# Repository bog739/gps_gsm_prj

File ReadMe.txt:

-> machine module is for generic board in contrast with pyb lib

-> This project was started with gps and gsm modules
on a simple plastic board with attached cables for
TTL conversion for USB and Pycharm was used to link up
with devices.

-> In meantime the development of this project started on Pi pico, and
Thonny IDE is used afterwards, MicroPython plugin for Pycharm is not
so great. Although, Thonny IDE needs some improvement for USB communication, but for this
issue a  reset button was attached for Pi pico to re-enable the communication.

-> There is a problem for matching modules to have a perfect synchronization as close as possible,
when working on a real PCB board, taking into consideration that components are not place as close as
possible to each other's pins which traces' inductance can increase substantialy.

-> For gps module a simple solution is to use a loop to wait for gps' data to come, but
this method is not very precise because of uncertainty of synchronization between python program and
how quick gps sends its data in its specific format.

-> Basic functions read, readline, write from UART module of micropython do not work
as expected, by using uasyncio lib with StreamWriter and StreamReader classes only then characters
are stored in UART buffer and read or written as wanted. From StreamWriter class use drain function after a write func
to output buffer data or just awrite method(it uses internally drain()).

Possibilities for gsm Ctrl-Z problem:
-> It takes some time to process, send and return a status for SMS so an
immediate read doesn't report anything. A subsequent read may.
I would keep issuing read until you get something other than nothing.

-> The GA6 isn't actioning the Ctrl-Z. Issuing a write 'ABC\r' and a read
should show if it's still in its waiting for message mode.

-> For some reason the Ctrl-Z isn't being sent to the GA6.
Again, issuing a write 'ABC\r' and a read should show if it's still in its waiting for message mode.

-> Looking at what gets sent out with a Terminal Emulator
instead of the GA6 should confirm whether Ctrl-Z's are sent or not.
Being the ASCII code for "EOF - End of File' imeans it could be handled differently
to printable ASCII codes, but if that's the case would how any other GA6 user has achieved it.

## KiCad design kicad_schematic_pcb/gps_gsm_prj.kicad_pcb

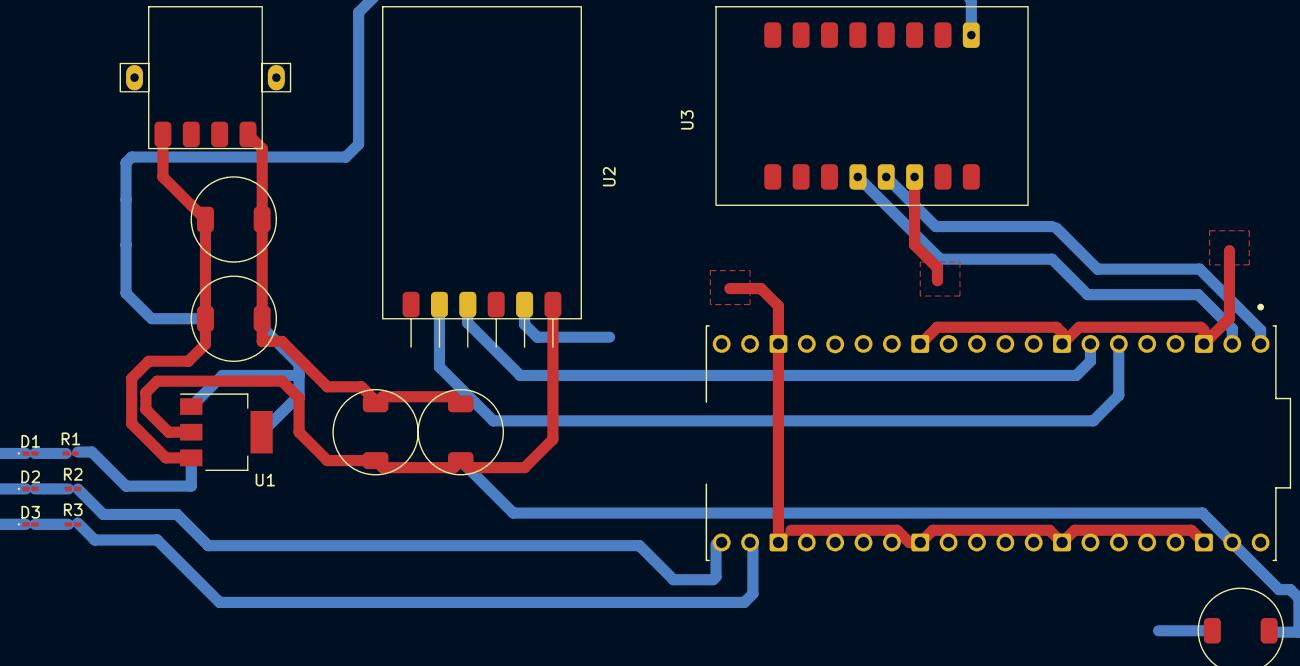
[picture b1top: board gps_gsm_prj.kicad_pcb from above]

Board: 2 copper layers, 16 parts (0 on the bottom side), 8 nets.

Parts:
A1: SC0915; MODULE_SC0915
C1, C2, C3, C4, C5: 10uF; cap
D1: LED_power; LED_0201_0603Metric_Pad0.64x0.40mm_HandSolder
D2: LED_gps; LED_0201_0603Metric_Pad0.64x0.40mm_HandSolder
D3: LED_gsm; LED_0201_0603Metric_Pad0.64x0.40mm_HandSolder
J1: USB_B; USB
R1: 300Ω; R_0201_0603Metric_Pad0.64x0.40mm_HandSolder
R2, R3: 10kΩ; R_0201_0603Metric_Pad0.64x0.40mm_HandSolder
U1: LD1117S33TR_SOT223; SOT-223-3_TabPin2
U2: Pmod_GPS; gps
U3: GSM_module; gsm

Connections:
/VU1_3V3: A1.39 (VSYS), C3.1, C4.1, C5.1, U1.2 (VO), U2.6 (Vcc)
/Vin_5V: C1.1, C2.1, J1.1 (VBUS), U1.3 (VI), U3.8 (Vcc)
GND: C1.2, C2.2, C3.2, C4.2, J1.4 (GND), U1.1 (GND), U1.2 (VO)
GND1: D1.1 (K), D1.2 (A), D2.1 (K), D2.2 (A), D3.1 (K), D3.2 (A), R1.1, R1.2, R2.1, R2.2, R3.1, R3.2
GND2: C5.2, U2.5 (GND), U3.14 (GND)
unnamed: A1.1 (GP0), U3.13 (Rx)
unnamed: A1.2 (GP1), U3.12 (Tx)
unnamed: A1.3 (GND), A1.4 (GP2), A1.5 (GP3), A1.6 (GP4), A1.7 (GP5), A1.8 (GND), A1.9 (GP6), A1.10 (GP7), A1.11 (GP8), A1.12 (GP9), A1.13 (GND), A1.14 (GP10), A1.15 (GP11), A1.16 (GP12), A1.17 (GP13), A1.18 (GND), A1.19 (GP14), A1.20 (GP15), A1.23 (GND), A1.24 (GP18), A1.25 (GP19), A1.26 (GP20), A1.27 (GP21), A1.28 (GND), A1.29 (GP22), A1.30 (RUN), A1.31 (GP26), A1.32 (GP27), A1.33 (AGND), A1.34 (GP28), A1.35 (ADC_VREF), A1.36 (3V3_OUT), A1.37 (3V3_EN), A1.38 (GND), U2.2 (RX), U2.3 (TX)

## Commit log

2022-11-06 First version for gps module, not fully compatible, gsm module class yet to come
2022-11-08 Added selection for gps and gsm on COM ports
2022-11-09 Added segmentation of data from gps
2022-11-15 GPS part done
2022-11-26 gsm class added dfe9ae1, selected AT commands of use
2022-12-01 started dev for pi pico, changes for all files may be needed
2022-12-01 a small refacto on main.py file to fit in Pi Pico
2022-12-01 added first readme file with some explanations on this project
2022-12-22 started developing schematic and pcb layout in KiCad
2023-01-06 Problems occured with UART communication, but using uasyncio lib aprox solved the issue
2023-01-06 updated readme.txt with extra explanations on different problems solved
2023-01-06 program version -> v0.1
2023-01-07 A good working version of the program from cc951017
2023-01-07 stable version -> v0.1
2023-01-15 KiCad files for schematic and PCB - v1.0
2023-01-15 documentation for project
2023-01-16 rearranged files in directories
2023-01-17 added proteus files
